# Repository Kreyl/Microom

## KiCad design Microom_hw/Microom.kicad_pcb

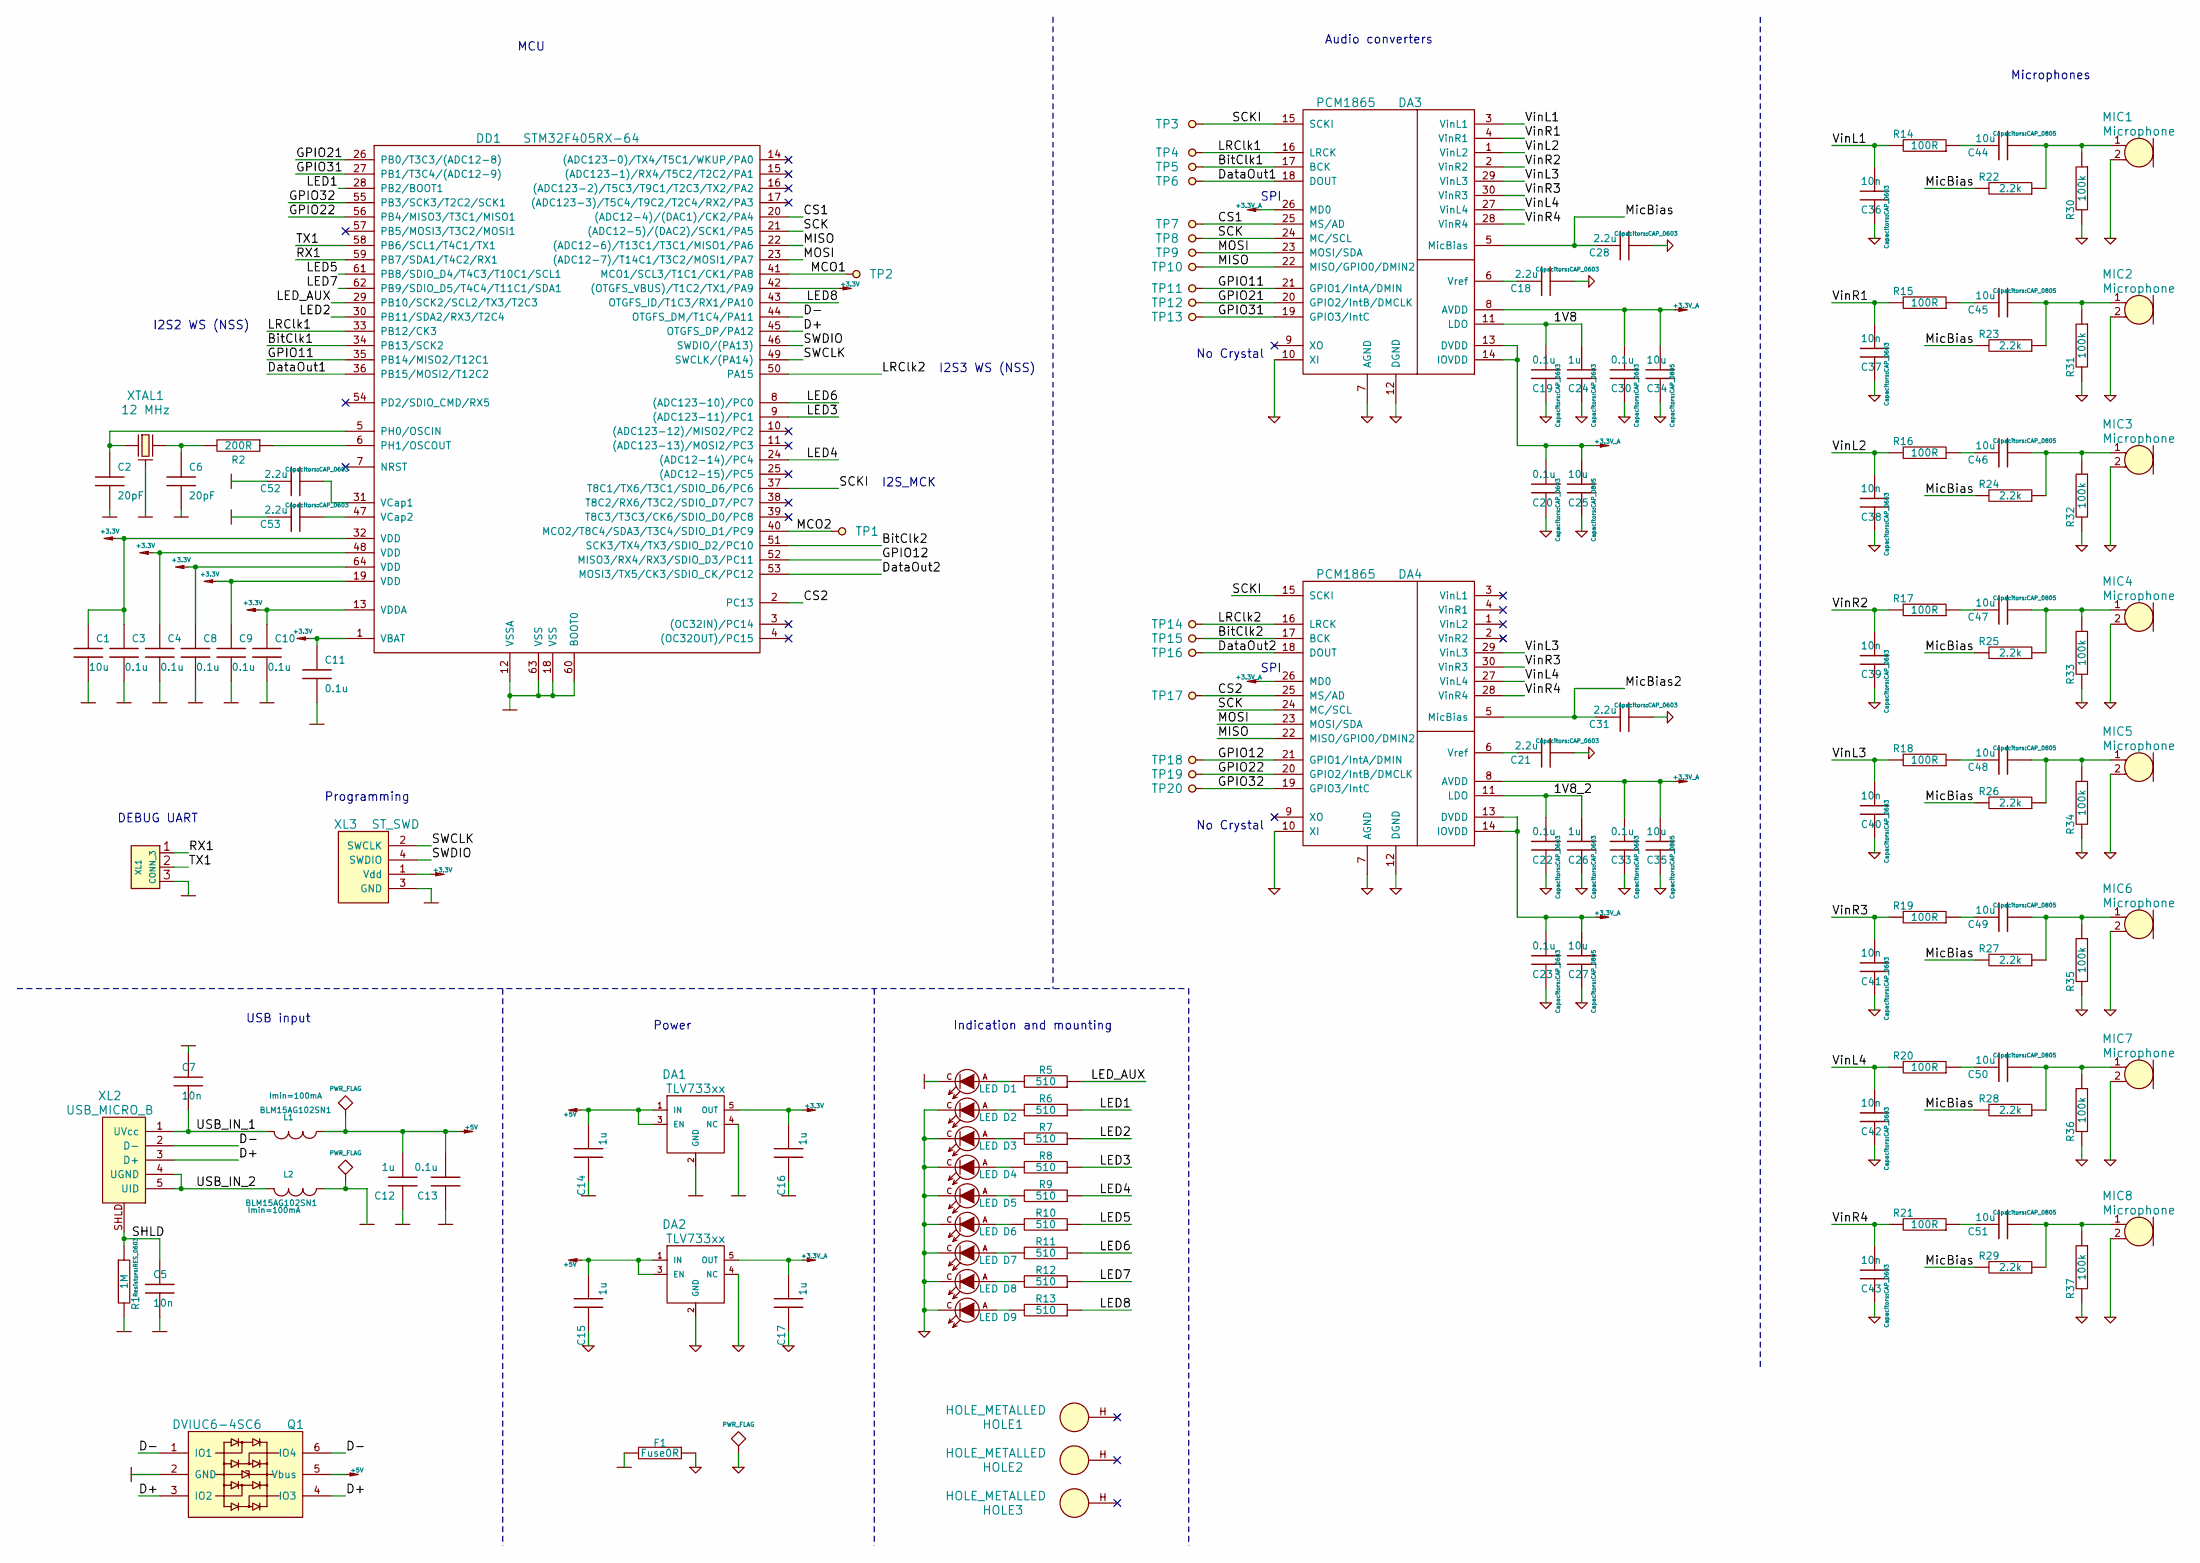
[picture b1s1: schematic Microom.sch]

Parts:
C1, C25, C27, C34, C35, C44, C45, C46, C47, C48, C49, C50, C51: 10u; CAP_0805
C2, C6: 20pF; CAP_0603
C3, C4, C8, C9, C10, C11, C13, C19, C20, C22, C23, C30, C33: 0.1u; CAP_0603
C5, C7, C36, C37, C38, C39, C40, C41, C42, C43: 10n; CAP_0603
C12, C14, C15, C16, C17, C24, C26: 1u; CAP_0603
C18, C21, C28, C31, C52, C53: 2.2u; CAP_0603
D1, D2, D3, D4, D5, D6, D7, D8, D9: LED; LED_0603
DA1, DA2: TLV733xx; SOT23-5
DA3, DA4: PCM1865; TSSOP30
DD1: STM32F405RX-64; LQFP64
F1: Fuse0R; RES_0603_SOLDERFUSE
HOLE1, HOLE2, HOLE3: HOLE_METALLED; Hole3_5_out6mm
L1, L2: BLM15AG102SN1; IND_0402
MIC1, MIC2, MIC3, MIC4, MIC5, MIC6, MIC7, MIC8: Microphone; PLS-2
Q1: DVIUC6-4SC6; SOT23-6
R1: 1M; RES_0603
R2: 200R; RES_0603
R5, R6, R7, R8, R9, R10, R11, R12, R13: 510; RES_0603
R14, R15, R16, R17, R18, R19, R20, R21: 100R; RES_0603
R22, R23, R24, R25, R26, R27, R28, R29: 2.2k; RES_0603
R30, R31, R32, R33, R34, R35, R36, R37: 100k; RES_0603
TP1, TP2, TP3, TP4, TP5, TP6, TP7, TP8, TP9, TP10, TP11, TP12, TP13, TP14, TP15, TP16, TP17, TP18, TP19, TP20: TESTPOINT; TESTPOINT_1MM
XL1: CONN_3; PLS-3
XL2: USB_MICRO_B; USBmicro_MOLEX_WM17142
XL3: ST_SWD; PLS-4
XTAL1: 12 MHz; 0503x4-4

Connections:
+3.3V: C1.1, C3.1, C4.1, C8.1, C9.1, C10.1, C11.1, C16.2, DA1.5 (OUT), DD1.1 (VBAT), DD1.13 (VDDA), DD1.19 (VDD), DD1.32 (VDD), DD1.42 ((OTGFS_VBUS)/T1C2/TX1/PA9), DD1.48 (VDD), DD1.64 (VDD), XL3.1 (Vdd)
+3.3V_A: C17.2, C20.1, C23.1, C25.1, C27.1, C30.1, C33.1, C34.1, C35.1, DA2.5 (OUT), DA3.8 (AVDD), DA3.13 (DVDD), DA3.14 (IOVDD), DA3.26 (MD0), DA4.8 (AVDD), DA4.13 (DVDD), DA4.14 (IOVDD), DA4.26 (MD0)
+5V: C12.2, C13.2, C14.2, C15.2, DA1.1 (IN), DA1.3 (EN), DA2.1 (IN), DA2.3 (EN), L1.1, Q1.5 (Vbus)
/1V8: C19.1, C24.1, DA3.11 (LDO)
/1V8_2: C22.1, C26.1, DA4.11 (LDO)
/BitClk1: DA3.17 (BCK), DD1.34 (PB13/SCK2), TP5.1
/BitClk2: DA4.17 (BCK), DD1.51 (SCK3/TX4/TX3/SDIO_D2/PC10), TP15.1
/CS1: DA3.25 (MS/AD), DD1.20 ((ADC12-4)/(DAC1)/CK2/PA4), TP7.1
/CS2: DA4.25 (MS/AD), DD1.2 (PC13), TP17.1
/D+: DD1.45 (OTGFS_DP/PA12), Q1.3 (IO2), Q1.4 (IO3), XL2.3 (D+)
/D-: DD1.44 (OTGFS_DM/T1C4/PA11), Q1.1 (IO1), Q1.6 (IO4), XL2.2 (D-)
/DataOut1: DA3.18 (DOUT), DD1.36 (PB15/MOSI2/T12C2), TP6.1
/DataOut2: DA4.18 (DOUT), DD1.53 (MOSI3/TX5/CK3/SDIO_CK/PC12), TP16.1
/GPIO11: DA3.21 (GPIO1/IntA/DMIN), DD1.35 (PB14/MISO2/T12C1), TP11.1
/GPIO12: DA4.21 (GPIO1/IntA/DMIN), DD1.52 (MISO3/RX4/RX3/SDIO_D3/PC11), TP18.1
/GPIO21: DA3.20 (GPIO2/IntB/DMCLK), DD1.26 (PB0/T3C3/(ADC12-8)), TP12.1
/GPIO22: DA4.20 (GPIO2/IntB/DMCLK), DD1.56 (PB4/MISO3/T3C1/MISO1), TP19.1
/GPIO31: DA3.19 (GPIO3/IntC), DD1.27 (PB1/T3C4/(ADC12-9)), TP13.1
/GPIO32: DA4.19 (GPIO3/IntC), DD1.55 (PB3/SCK3/T2C2/SCK1), TP20.1
/LED1: DD1.28 (PB2/BOOT1), R6.1
/LED2: DD1.30 (PB11/SDA2/RX3/T2C4), R7.1
/LED3: DD1.9 ((ADC123-11)/PC1), R8.1
/LED4: DD1.24 ((ADC12-14)/PC4), R9.1
/LED5: DD1.61 (PB8/SDIO_D4/T4C3/T10C1/SCL1), R10.1
/LED6: DD1.8 ((ADC123-10)/PC0), R11.1
/LED7: DD1.62 (PB9/SDIO_D5/T4C4/T11C1/SDA1), R12.1
/LED8: DD1.43 (OTGFS_ID/T1C3/RX1/PA10), R13.1
/LED_AUX: DD1.29 (PB10/SCK2/SCL2/TX3/T2C3), R5.1
/LRClk1: DA3.16 (LRCK), DD1.33 (PB12/CK3), TP4.1
/LRClk2: DA4.16 (LRCK), DD1.50 (PA15), TP14.1
/MCO1: DD1.41 (MCO1/SCL3/T1C1/CK1/PA8), TP2.1
/MCO2: DD1.40 (MCO2/T8C4/SDA3/T3C4/SDIO_D1/PC9), TP1.1
/MISO: DA3.22 (MISO/GPIO0/DMIN2), DA4.22 (MISO/GPIO0/DMIN2), DD1.22 ((ADC12-6)/T13C1/T3C1/MISO1/PA6), TP10.1
/MOSI: DA3.23 (MOSI/SDA), DA4.23 (MOSI/SDA), DD1.23 ((ADC12-7)/T14C1/T3C2/MOSI1/PA7), TP9.1
/MicBias: C28.1, DA3.5 (MicBias), R22.2, R23.2, R24.2, R25.2, R26.2, R27.2, R28.2, R29.2
/MicBias2: C31.1, DA4.5 (MicBias)
/RX1: DD1.59 (PB7/SDA1/T4C2/RX1), XL1.1
/SCK: DA3.24 (MC/SCL), DA4.24 (MC/SCL), DD1.21 ((ADC12-5)/(DAC2)/SCK1/PA5), TP8.1
/SCKI: DA3.15 (SCKI), DA4.15 (SCKI), DD1.37 (T8C1/TX6/T3C1/SDIO_D6/PC6), TP3.1
/SHLD: C5.1, R1.1, XL2.SHLD
/SWCLK: DD1.49 (SWCLK/(PA14)), XL3.2 (SWCLK)
/SWDIO: DD1.46 (SWDIO/(PA13)), XL3.4 (SWDIO)
/TX1: DD1.58 (PB6/SCL1/T4C1/TX1), XL1.2 (PM)
/USB_IN_1: C7.2, L1.2, XL2.1 (UVcc)
/USB_IN_2: L2.2, XL2.4 (UGND), XL2.5 (UID)
/VinL1: C36.1, DA3.3 (VinL1), R14.2
/VinL2: C38.1, DA3.1 (VinL2), R16.2
/VinL3: C40.1, DA3.29 (VinL3), DA4.29 (VinL3), R18.2
/VinL4: C42.1, DA3.27 (VinL4), DA4.27 (VinL4), R20.2
/VinR1: C37.1, DA3.4 (VinR1), R15.2
/VinR2: C39.1, DA3.2 (VinR2), R17.2
/VinR3: C41.1, DA3.30 (VinR3), DA4.30 (VinR3), R19.2
/VinR4: C43.1, DA3.28 (VinR4), DA4.28 (VinR4), R21.2
AGND: C15.1, C17.1, C18.2, C19.2, C20.2, C21.2, C22.2, C23.2, C24.2, C25.2, C26.2, C27.2, C28.2, C30.2, C31.2, C33.2, C34.2, C35.2, C36.2, C37.2, C38.2, C39.2, C40.2, C41.2, C42.2, C43.2, D2.C, D3.C, D4.C, D5.C, D6.C, D7.C, D8.C, D9.C, DA2.2 (GND), DA2.4 (NC), DA3.7 (AGND), DA3.10 (XI), DA3.12 (DGND), DA4.7 (AGND), DA4.10 (XI), DA4.12 (DGND), F1.1, MIC1.2, MIC2.2, MIC3.2, MIC4.2, MIC5.2, MIC6.2, MIC7.2, MIC8.2, R30.2, R31.2, R32.2, R33.2, R34.2, R35.2, R36.2, R37.2
GND: C1.2, C2.2, C3.2, C4.2, C5.2, C6.2, C7.1, C8.2, C9.2, C10.2, C11.2, C12.1, C13.1, C14.1, C16.1, C52.1, C53.1, D1.C, DA1.2 (GND), DA1.4 (NC), DD1.12 (VSSA), DD1.18 (VSS), DD1.60 (BOOT0), DD1.63 (VSS), F1.2, L2.1, Q1.2 (GND), R1.2, XL1.3, XL3.3 (GND), XTAL1.H
unnamed: C2.1, DD1.5 (PH0/OSCIN), XTAL1.1
unnamed: C6.1, R2.2, XTAL1.2
unnamed: C18.1, DA3.6 (Vref)
unnamed: C21.1, DA4.6 (Vref)
unnamed: C44.1, R14.1
unnamed: C44.2, MIC1.1, R22.1, R30.1
unnamed: C45.1, R15.1
unnamed: C45.2, MIC2.1, R23.1, R31.1
unnamed: C46.1, R16.1
unnamed: C46.2, MIC3.1, R24.1, R32.1
unnamed: C47.1, R17.1
unnamed: C47.2, MIC4.1, R25.1, R33.1
unnamed: C48.1, R18.1
unnamed: C48.2, MIC5.1, R26.1, R34.1
unnamed: C49.1, R19.1
unnamed: C49.2, MIC6.1, R27.1, R35.1
unnamed: C50.1, R20.1
unnamed: C50.2, MIC7.1, R28.1, R36.1
unnamed: C51.1, R21.1
unnamed: C51.2, MIC8.1, R29.1, R37.1
unnamed: C52.2, DD1.31 (VCap1)
unnamed: C53.2, DD1.47 (VCap2)
unnamed: D1.A, R5.2
unnamed: D2.A, R6.2
unnamed: D3.A, R7.2
unnamed: D4.A, R8.2
unnamed: D5.A, R9.2
unnamed: D6.A, R10.2
unnamed: D7.A, R11.2
unnamed: D8.A, R12.2
unnamed: D9.A, R13.2
unnamed: DD1.6 (PH1/OSCOUT), R2.1

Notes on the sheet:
Power
DEBUG UART
Programming
USB input
SPI
I2S_MCK
I2S2 WS (NSS)
No Crystal
Microphones
Indication and mounting
MCU
Audio converters
I2S3 WS (NSS)

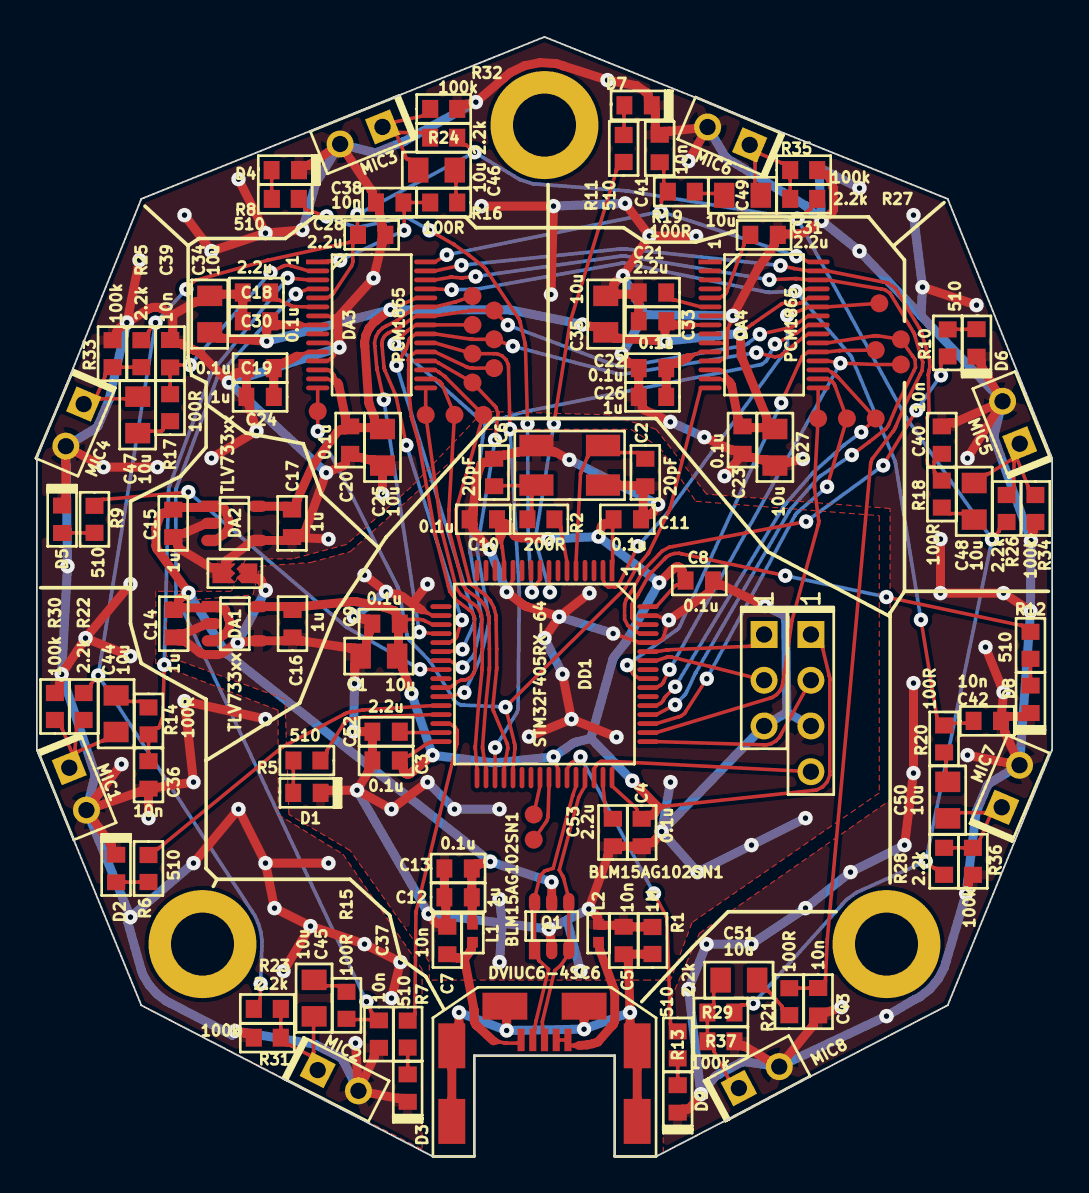
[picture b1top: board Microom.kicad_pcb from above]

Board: 2 copper layers, 56.4 x 62.2 mm, 139 parts (0 on the bottom side), 87 nets.

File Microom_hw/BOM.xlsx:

Reference | Quantity | Value | Footprint | Comment | Availability | Price | Summ
C1 C25 C27 C34 C35 C44 C45 C46 C47 C48 C49 C50 C51 | 13 | 10u | Capacitors:CAP_0805 |  | Надо добыть | 5 | 65
C12 C14 C15 C16 C17 C24 C26 | 7 | 1u | Capacitors:CAP_0603 |  | Есть | 3 | 21
C18 C21 C28 C31 C52 C53 | 6 | 2.2u | Capacitors:CAP_0603 |  | Есть | 3 | 18
C10 C11 C13 C19 C20 C22 C23 C3 C30 C33 C4 C8 C9 | 13 | 0.1u | Capacitors:CAP_0603 |  | Есть | 1 | 13
C2 C6 | 2 | 20pF | Capacitors:CAP_0603 |  | Есть | 1 | 2
C36 C37 C38 C39 C40 C41 C42 C43 C5 C7 | 10 | 10n | Capacitors:CAP_0603 |  | Есть | 1 | 10
D1 D2 D3 D4 D5 D6 D7 D8 D9 | 9 | LED | LEDs:LED_0603 |  | Заказано | 24 | 216
DA1 DA2 | 2 | TLV733xx | SOT:SOT23-5 | Power IC | Заказано | 25 | 50
DA3 DA4 | 2 | PCM1865 | SO_DIL_TSSOP:TSSOP30 | Audio ADC | Заказано |  | 0
DD1 | 1 | STM32F405RX-64 | LQFP_TQFP:LQFP64 | MCU | Заказано | 770 | 770
L1 L2 | 2 | BLM15AG102SN1 | Inductors:IND_0402 | USB Power filtering | Есть | 0.5 | 1
MIC1 MIC2 MIC3 MIC4 MIC5 MIC6 MIC7 MIC8 | 8 | Microphone | Connectors:PLS-2 |  | Для начала есть |  | 0
Q1 | 1 | DVIUC6-4SC6 | SOT:SOT23-6 | USB protection | Надо добыть | 80.5 | 80.5
R1 | 1 | 1M | Resistors:RES_0603 |  | Есть | 0.5 | 0.5
R14 R15 R16 R17 R18 R19 R20 R21 | 8 | 100R | Resistors:RES_0603 |  | Есть | 0.5 | 4
R2 | 1 | 200R | Resistors:RES_0603 |  | Есть | 0.5 | 0.5
R22 R23 R24 R25 R26 R27 R28 R29 | 8 | 2.2k | Resistors:RES_0603 |  | Поставим 2.7 | 0.5 | 4
R30 R31 R32 R33 R34 R35 R36 R37 | 8 | 100k | Resistors:RES_0603 |  | Есть | 0.5 | 4
R10 R11 R12 R13 R5 R6 R7 R8 R9 | 9 | 510 | Resistors:RES_0603 |  | Есть | 0.5 | 4.5
XL1 | 1 | CONN_3 | Connectors:PLS-3 |  | Есть | 3 | 3
XL2 | 1 | USB_MICRO_B | Connectors:USBmicro_MOLEX_WM17142 |  | Есть | 40 | 40
XL3 | 1 | ST_SWD | Connectors:PLS-4 |  | Есть | 4 | 4
XTAL1 | 1 | 12 MHz | Quartz:0503x4-4 |  | Есть | 40 | 40
Печатная плата | 1 |  |  | Точной цены еще нет | Заказано | 1250 | 1250
 |  |  |  |  |  | Итого | 2601
PCB details
F1 | 1 | Fuse0R | Resistors:RES_0603_SOLDERFUSE | Just solder it
HOLE1 HOLE2 HOLE3 | 3 | HOLE_METALLED | PCB:Hole3_5_out6mm
TP1 TP10 TP11 TP12 TP13 TP14 TP15 TP16 TP17 TP18 TP19 TP2 TP20 TP3 TP4 TP5 TP6 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 | 20 | TESTPOINT | PCB:TESTPOINT_1MM

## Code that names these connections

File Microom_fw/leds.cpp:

/*
 * leds.cpp
 *
 *  Created on: 27 ñåíò. 2015 ã.
 *      Author: Kreyl
 */

#include "leds.h"

PinOutput_t Led[9] = {
        {LEDAUX_GPIO, LEDAUX_PIN, omPushPull}, // Led[0] is AUX
        // LED[n] located near Mic[n]
        {LED1_GPIO, LED1_PIN, omPushPull},
        {LED2_GPIO, LED2_PIN, omPushPull},
        {LED3_GPIO, LED3_PIN, omPushPull},
        {LED4_GPIO, LED4_PIN, omPushPull},
        {LED5_GPIO, LED5_PIN, omPushPull},
        {LED6_GPIO, LED6_PIN, omPushPull},
        {LED7_GPIO, LED7_PIN, omPushPull},
        {LED8_GPIO, LED8_PIN, omPushPull},
};

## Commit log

2015-08-18 + Sch 20% completed
2015-08-19 Sch 50% complete
2015-08-20 Sch 100% completed
2015-08-21 PCB routing started, components put on board
2015-08-21 * Components spread over the board
2015-08-22 * PCB routing 30% completed
2015-08-22 Routing done, GND planes not placed yet.
2015-08-22 + PCB completed and sent to production + BOM
2015-08-22 + Firmware OS v.2.6.8
2015-08-23 Switch to Chibios v.3.0.1. Project compiled successfully, but not tested on hardware.
2015-09-03 * Fixed in-IRQ freezing bug (USE_FPU added)
2015-09-03 + USB CDC class implemented and works
2015-09-03 * USB CDC moved to class Repeater implemented, but there is something strange with printf.
2015-09-04 + Audio descriptors - CDC descriptors Compiled, device found, but SetSetting not implemented.
2015-09-05 * Host sees device as microphone
2015-09-05 Test signal is transmitted through USB
2015-09-10 + Clocking MCO2 output + Trying to setup PCM1865
2015-09-12 + PCM1865 answers its state
2015-09-12 + UART RX
2015-09-12 + Uart cmds: State, Run, PwrDwn Init seems working.
2015-09-12 * All board settings moved to board.h + I2S DMA implemented
2015-09-16 Switching to queue
2015-09-17 Queues removed, USB transmission fixed.
2015-09-24 * Left / right channel separated, MSB mode implemented
2015-09-25 * Reading pair of mics a time.
2015-09-26 * Hand-tuned PLL seems working. No data output, though.
2015-09-27 Hand-tuned PLL works somehow, and output produced. Wrong fs, though.
2015-09-27 Correct fs
2015-09-27 4 channels transmitted, reception is not implemented yet
2015-09-27 Code clean-up
2015-09-29 + LEDs * Switching to 4-mic solution + Gain control by UART
2015-09-29 + Leds aliased to mics + Averaging Level detector implemented + LEDs indicate loudest signal
2015-09-29 * Level detector is now IIR (faster, less memory)
2015-09-29 * Switched to Fs = 8kHz
2015-09-30 * Code clean-up
2015-10-13 * Lvl Meter switched to moving average Currently no Automatic Gain Control
2015-10-15 + AGC * LvlMtr set up with template
2015-10-15 + 16 kHz added: switched by define
2015-10-19 * BOM actualized
2015-10-24 * 16kHz only
2015-10-29 * lib updated, shell added
2015-10-29 * Proceeding with keyboard
2015-11-01 + Keyboard found TODO: other USB VID/PID
2015-11-01 Key 'a' is sent, but non-stoppable
2015-11-02 + Keys buffer + Keyboard works ok
2015-11-02 + ADC works and sees sensors
2015-11-02 + Gesture recognition
2015-11-02 + Keyboard signalling enabled
2015-11-07 Minor changes
2015-11-07 + APDS9960 * I2C udated
2015-11-07 + Init seems completed
2015-11-07 Proceeding + Fifo read implemented
2015-11-08 Proceeding + averaging values
2015-11-08 + Excel algorithm realization + Seems working
2015-11-08 * USB enabled Release candidate
2015-11-08 +cases and microom pcb sldrp
2015-11-08 + Case + Mic + APDS PCB
2015-11-08 Proceeding wit cases
2015-11-08 Proceeding
2015-11-08 Case seems completed
2015-11-10 + New recognition algorythm
2015-11-11 + Timeout data reset
2015-11-11 + SnsHolder * ADC switched to other chnl due to contact pad extermination
2015-11-26 Proceeding with LEDs
2015-11-27 + level demonstrated with leds
2015-12-01 Mics soldered to places 2,5,7,8 (R1, L3, L4, R4) * Groups are changed accordingly
2015-12-01 + Terminal macro + Channel select both auto and by command
